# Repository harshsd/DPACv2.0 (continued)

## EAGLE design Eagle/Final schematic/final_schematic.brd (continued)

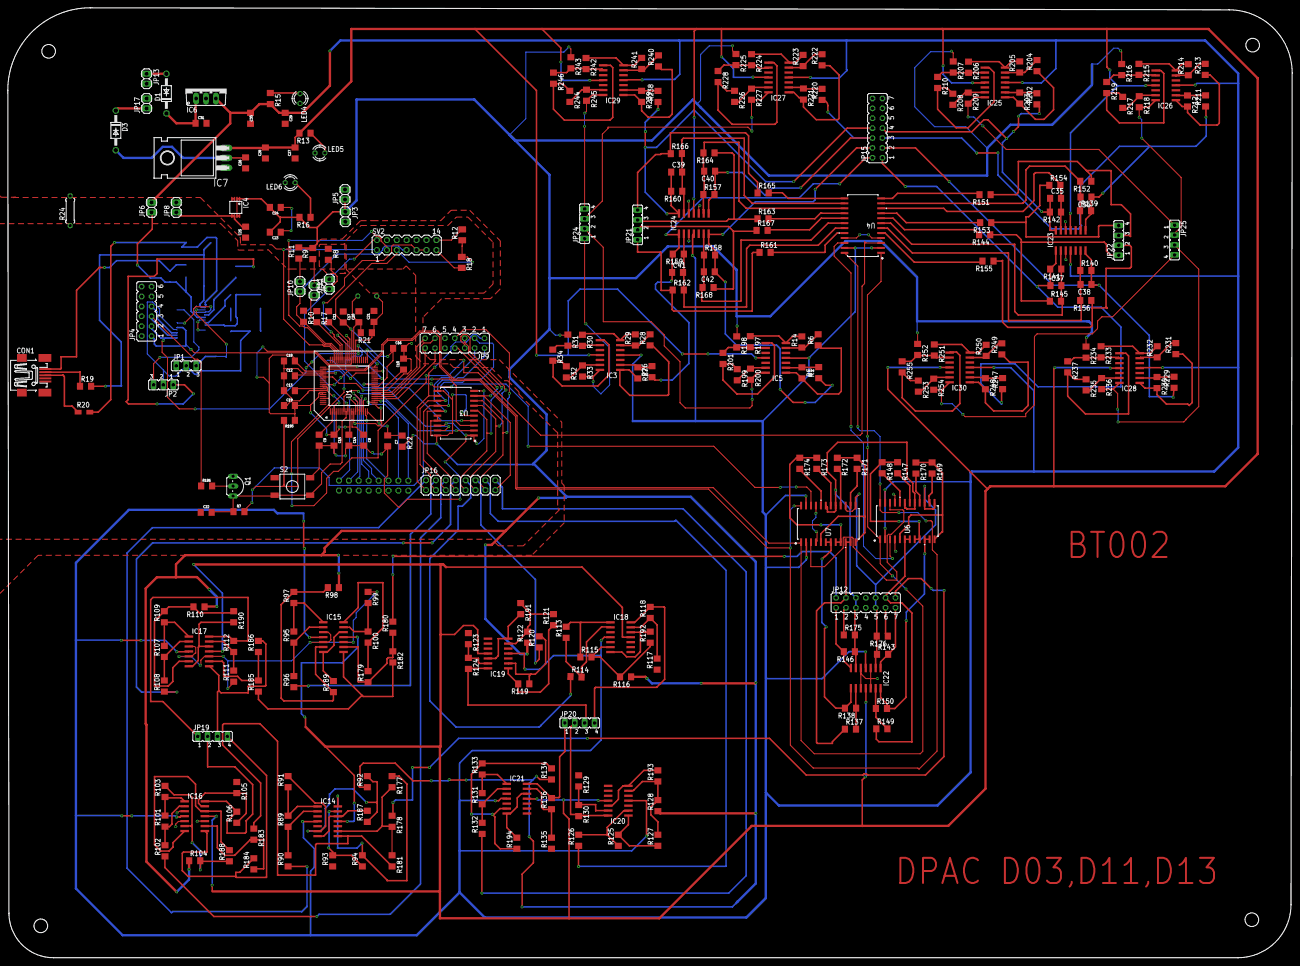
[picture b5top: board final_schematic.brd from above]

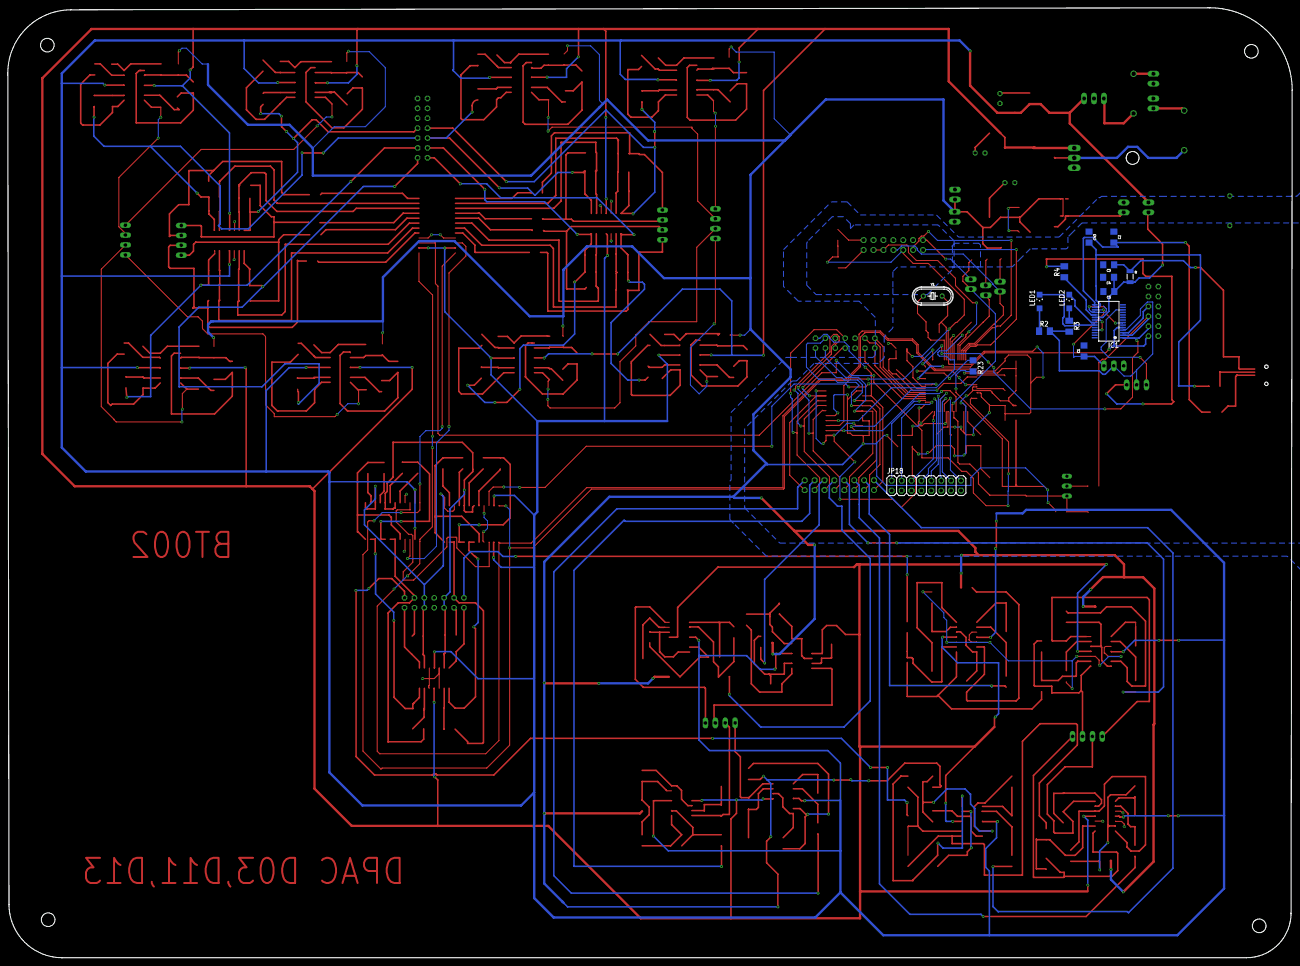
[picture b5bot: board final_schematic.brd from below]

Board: 2 copper layers, 329.5 x 243.7 mm, 303 parts (16 on the bottom side), 272 nets.

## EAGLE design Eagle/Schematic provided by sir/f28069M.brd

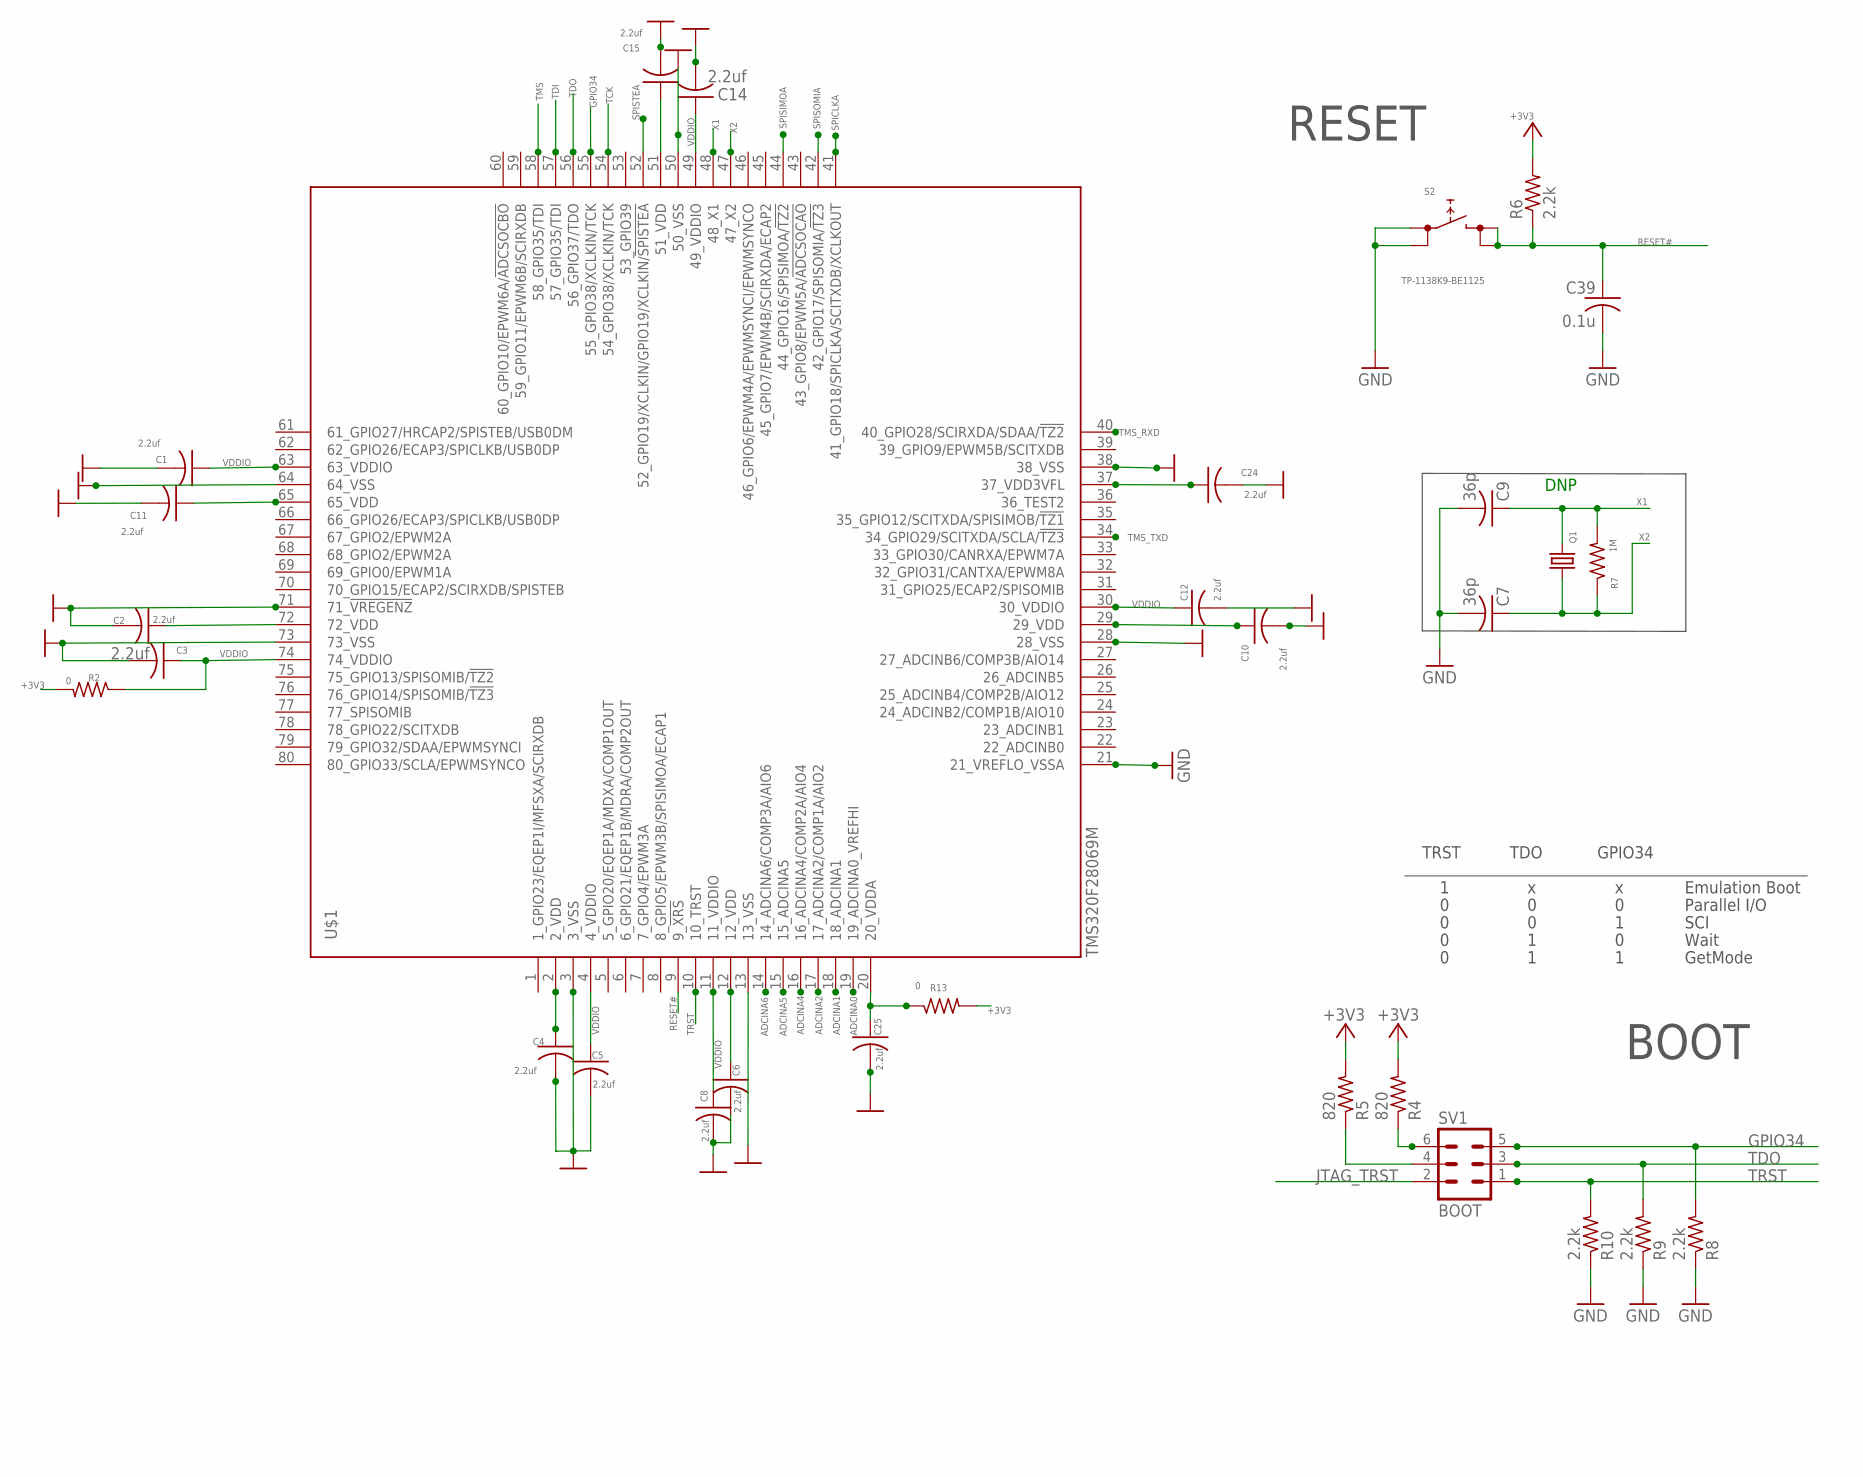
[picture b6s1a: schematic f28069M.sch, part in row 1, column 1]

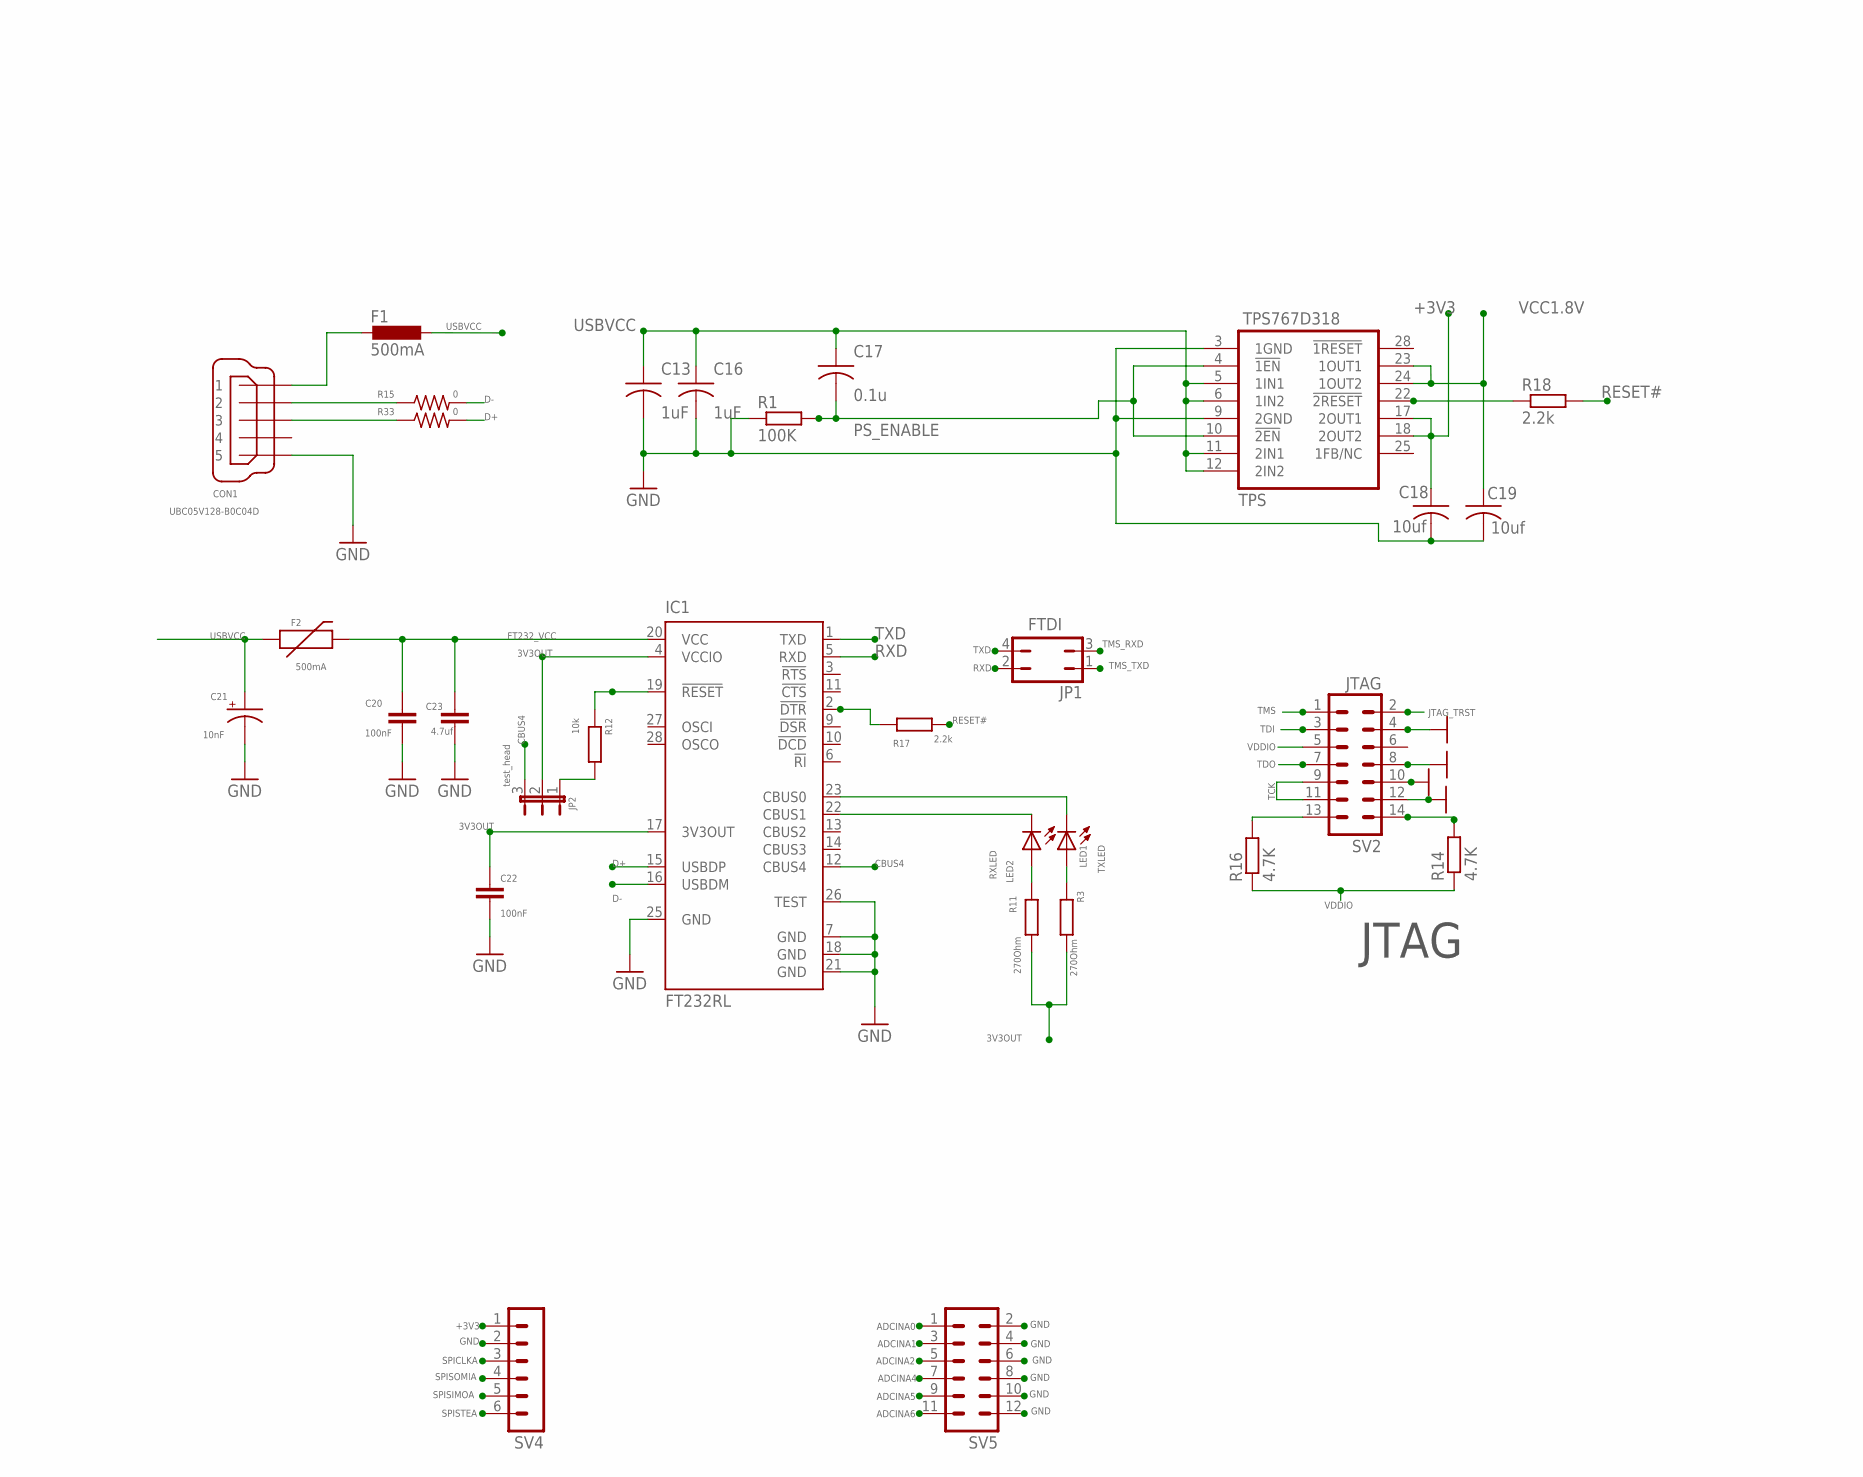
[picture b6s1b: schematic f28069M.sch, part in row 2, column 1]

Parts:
C1, C2, C3, C4, C5, C6, C8, C10, C11, C12, C14, C15, C24, C25: 2.2uf; C1206K
C7, C9: 36p; C1206K
C13, C16: 1uF; C-2,5
C17: 0.1u; C-2,5
C18, C19: 10uf; C-2,5
C20, C22: 100nF; 1210
C21: 10nF; EIA3216
C23: 4.7uf; C2.5-3
C39: 0.1u; C1206K
CON1: UBC05V128-B0C04D; 32005-201
F1: 500mA; L1812
F2: 500mA; PTC-1206
IC1: FT232RL; SSOP28
JP1: FTDI; JP2Q
JP2: test_head; JP2
LED1: TXLED; CHIPLED_1206
LED2: RXLED; CHIPLED_1206
Q1: CRYSTALHC49S; HC49/S
R1: 100K; M1206
R2, R13, R15: 0; R1206
R3, R11: 270Ohm; M1206
R4, R5: 820; R1206
R6, R8, R9, R10: 2.2k; R1206
R7: 1M; R1206
R12: 10k; M1206
R14, R16: 4.7K; M1206
R17, R18: 2.2k; M1206
R33: 0; R1206W
S2: TP-1138K9-BE1125; FSMJSMA
SV1: BOOT; MA03-2
SV2: JTAG; MA07-2
SV4: MA06-1
SV5: MA06-2
TPS: TPS767D318; 767D3XX
U$1: TMS320F28069M; S-PQFP-G80

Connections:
3V3OUT: C22.1, IC1.4 (VCCIO), IC1.17 (3V3OUT), JP2.2, R3.2, R11.2
+3V3: C18.1, R2.2, R4.2, R5.2, R6.2, R13.2, SV4.1, TPS.17 (2OUT1), TPS.18 (2OUT2)
ADCINA0: SV5.1, U$1.19 (19_ADCINA0_VREFHI)
ADCINA1: SV5.3, U$1.18 (18_ADCINA1)
ADCINA2: SV5.5, U$1.17 (17_ADCINA2/COMP1A/AIO2)
ADCINA4: SV5.7, U$1.16 (16_ADCINA4/COMP2A/AIO4)
ADCINA5: SV5.9, U$1.15 (15_ADCINA5)
ADCINA6: SV5.11, U$1.14 (14_ADCINA6/COMP3A/AIO6)
CBUS4: IC1.12 (CBUS4), JP2.3
D+: IC1.15 (USBDP), R33.2
D-: IC1.16 (USBDM), R15.2
FT232_VCC: C20.1, C23.1, F2.2, IC1.20 (VCC)
GND: C1.2, C2.2, C3.2, C4.2, C5.2, C6.2, C7.2, C8.2, C9.2, C10.2, C11.2, C12.2, C13.2, C14.2, C15.2, C16.2, C18.2, C19.2, C20.2, C21.C (-), C22.2, C23.2, C24.2, C25.2, C39.2, CON1.5, IC1.7 (GND), IC1.18 (GND), IC1.21 (GND), IC1.25 (GND), IC1.26 (TEST), R1.1, R8.1, R9.1, R10.1, S2.P$1 (0), S2.P$2 (0), SV2.4, SV2.8, SV2.10, SV2.12, SV4.2, SV5.2, SV5.4, SV5.6, SV5.8, SV5.10, SV5.12, TPS.3 (1GND), TPS.9 (2GND), U$1.3 (3_VSS), U$1.13 (13_VSS), U$1.21 (21_VREFLO_VSSA), U$1.28 (28_VSS), U$1.38 (38_VSS), U$1.50 (50_VSS), U$1.64 (64_VSS), U$1.71 (71_!VREGENZ), U$1.73 (73_VSS)
GPIO34: R8.2, SV1.5, U$1.55 (55_GPIO38/XCLKIN/TCK)
JTAG_TRST: SV1.2, SV2.2
unnamed: C10.1, U$1.29 (29_VDD)
unnamed: R16.2, SV2.13
unnamed: C15.1, U$1.51 (51_VDD)
unnamed: C24.1, U$1.37 (37_VDD3VFL)
unnamed: R4.1, SV1.6
unnamed: R5.1, SV1.4
unnamed: R14.2, SV2.14
unnamed: C11.1, U$1.65 (65_VDD)
unnamed: IC1.2 (!DTR), R17.1
unnamed: R18.1, TPS.22 (!2RESET)
unnamed: C2.1, U$1.72 (72_VDD)
unnamed: C4.1, U$1.2 (2_VDD)
unnamed: C6.1, U$1.12 (12_VDD)
unnamed: LED1.A, R3.1
unnamed: LED2.A, R11.1
unnamed: IC1.23 (CBUS0), LED1.C
unnamed: IC1.22 (CBUS1), LED2.C
unnamed: JP2.1, R12.2
unnamed: CON1.2, R15.1
unnamed: CON1.3, R33.1
PS_ENABLE: C17.2, R1.2, TPS.4 (!1EN), TPS.10 (!2EN)
RESET: IC1.19 (!RESET), R12.1
RESET#: C39.1, R6.1, R17.2, R18.2, S2.P$3 (1), S2.P$4 (1), U$1.9 (9_!XRS)
RXD: IC1.5 (RXD), JP1.2
SPICLKA: SV4.3, U$1.41 (41_GPIO18/SPICLKA/SCITXDB/XCLKOUT)
SPISIMOA: SV4.5, U$1.44 (44_GPIO16/SPISIMOA/!TZ2)
SPISOMIA: SV4.4, U$1.42 (42_GPIO17/SPISOMIA/!TZ3)
SPISTEA: SV4.6, U$1.52 (52_GPIO19/XCLKIN/GPIO19/XCLKIN/!SPISTEA)
TCK: SV2.9, SV2.11, U$1.54 (54_GPIO38/XCLKIN/TCK)
TDI: SV2.3, U$1.57 (57_GPIO35/TDI)
TDO: R9.2, SV1.3, SV2.7, U$1.56 (56_GPIO37/TDO)
TMS: SV2.1, U$1.58 (58_GPIO35/TDI)
TMS_RXD: JP1.3, U$1.40 (40_GPIO28/SCIRXDA/SDAA/!TZ2)
TMS_TXD: JP1.1, U$1.34 (34_GPIO29/SCITXDA/SCLA/!TZ3)
TRST: R10.2, SV1.1, U$1.10 (10_TRST)
TXD: IC1.1 (TXD), JP1.4
USBVCC: C13.1, C16.1, C17.1, C21.A (+), F1.1, F2.1, TPS.5 (1IN1), TPS.6 (1IN2), TPS.11 (2IN1), TPS.12 (2IN2)
VCC1.8V: C19.1, TPS.23 (1OUT1), TPS.24 (1OUT2)
VDDA: C25.1, R13.1, U$1.20 (20_VDDA)
VDDIO: C1.1, C3.1, C5.1, C8.1, C12.1, C14.1, R2.1, R14.1, R16.1, SV2.5, U$1.4 (4_VDDIO), U$1.11 (11_VDDIO), U$1.30 (30_VDDIO), U$1.49 (49_VDDIO), U$1.63 (63_VDDIO), U$1.74 (74_VDDIO)
X1: C9.1, Q1.2, R7.2, U$1.48 (48_X1)
X2: C7.1, Q1.1, R7.1, U$1.47 (47_X2)
XUSB: CON1.1, F1.2

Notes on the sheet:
RESET
TDO
GPIO34
TRST
Emulation Boot
Parallel I/O
SCI
Wait
GetMode
BOOT
DNP
JTAG

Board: 2 copper layers, 61 parts (0 on the bottom side), 58 nets, no tracks yet.

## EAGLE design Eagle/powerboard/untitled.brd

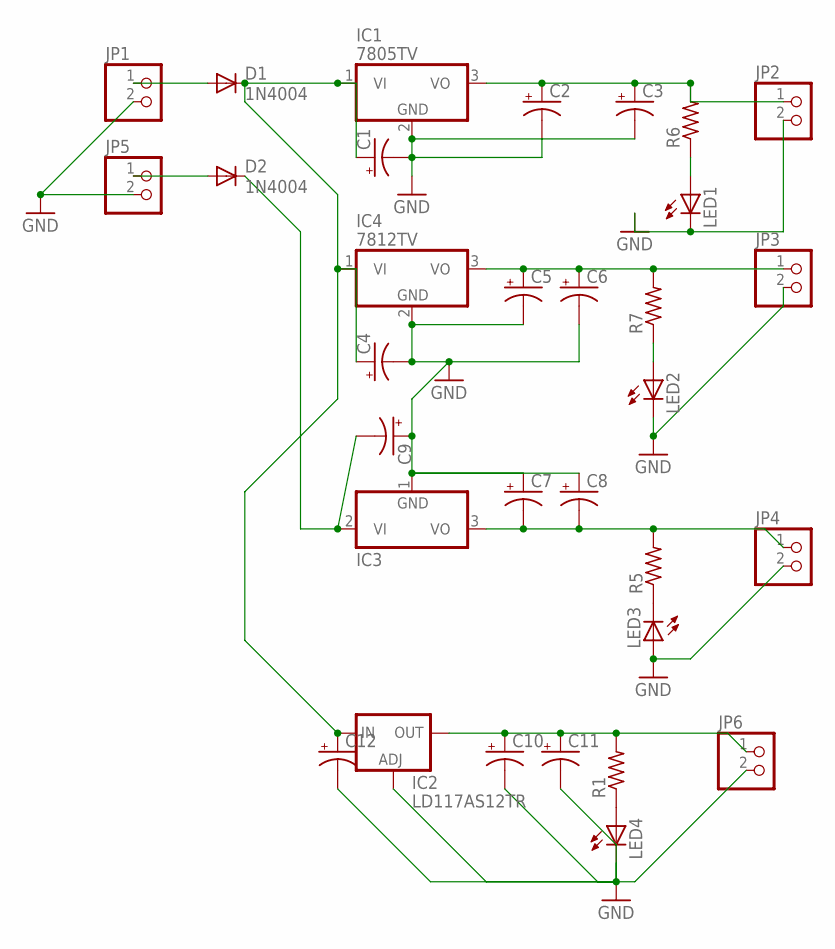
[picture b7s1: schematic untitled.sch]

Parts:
C1, C2, C3, C4, C5, C6, C7, C8, C9, C10, C11, C12: CPOL-USE2.5-5; E2,5-5
D1, D2: 1N4004; DO41-10
IC1: 7805TV; TO220V
IC2: LD117AS12TR; SOT223
IC3: 7912T; TO220H
IC4: 7812TV; TO220V
JP1, JP2, JP3, JP4, JP5, JP6: PINHD-1X2; 1X02
LED1, LED2, LED3, LED4: LED3MM
R1, R5, R6, R7: R-US_R1206; R1206

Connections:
GND: C1.-, C2.-, C3.-, C4.-, C5.-, C6.-, C7.+, C8.+, C9.+, C10.-, C11.-, C12.-, IC1.2 (GND), IC2.1 (ADJ), IC3.1 (GND), IC4.2 (GND), JP1.2, JP2.2, JP3.2, JP4.2, JP5.2, JP6.2, LED1.K (C), LED2.K (C), LED3.A, LED4.K (C)
unnamed: D1.A, JP1.1
unnamed: C9.-, D2.C, IC3.2 (VI)
unnamed: D2.A, JP5.1
unnamed: LED4.A, R1.1
unnamed: LED1.A, R6.1
unnamed: C2.+, C3.+, IC1.3 (VO), JP2.1, R6.2
unnamed: C5.+, C6.+, IC4.3 (VO), JP3.1, R7.2
unnamed: LED2.A, R7.1
unnamed: LED3.K (C), R5.1
unnamed: C7.-, C8.-, IC3.3 (VO), JP4.1, R5.2
unnamed: C1.+, C4.+, C12.+, D1.C, IC1.1 (VI), IC2.3 (IN), IC4.1 (VI)
unnamed: C10.+, C11.+, IC2.4 (OUT), JP6.1, R1.2

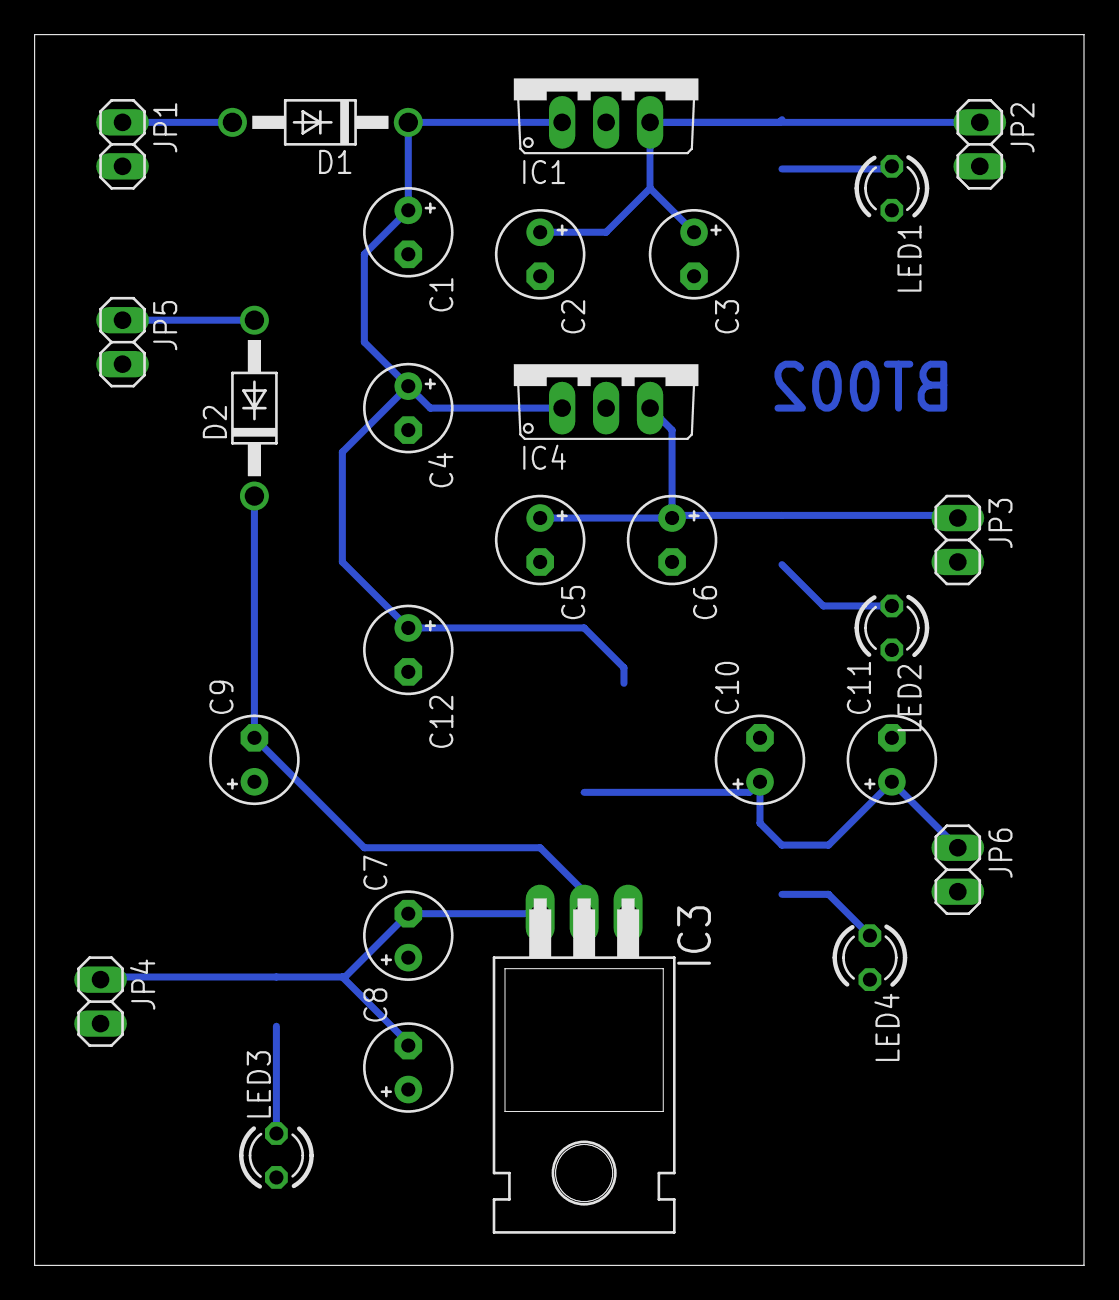
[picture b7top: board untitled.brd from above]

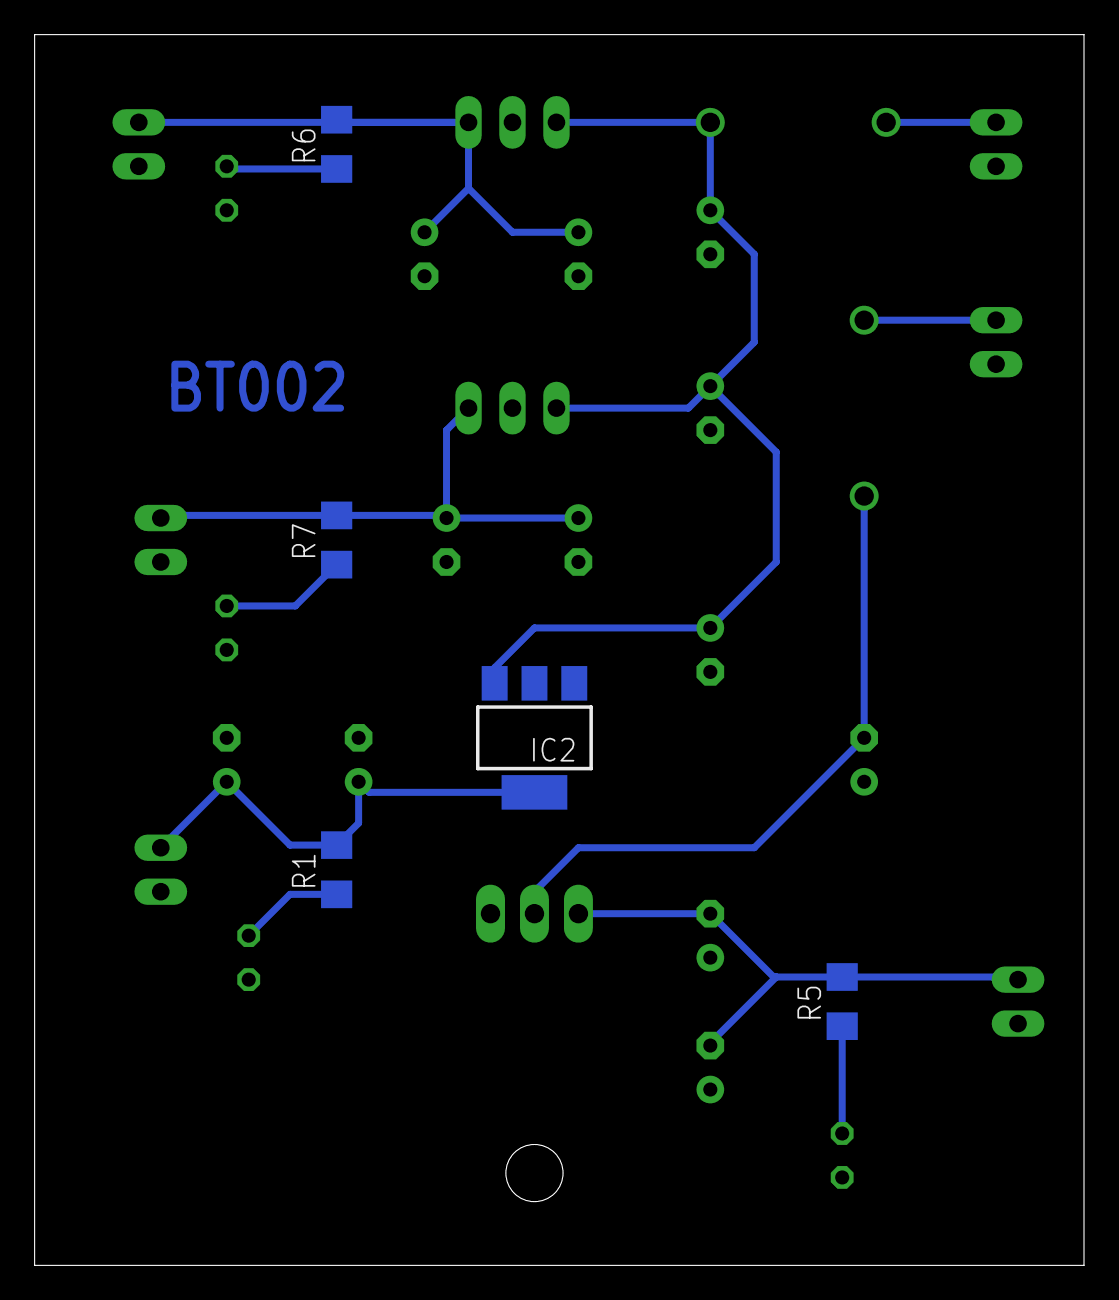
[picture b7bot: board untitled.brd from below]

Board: 2 copper layers, 60.6 x 71.1 mm, 32 parts (5 on the bottom side), 13 nets.

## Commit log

2019-04-15 C++ code left
2019-04-18 test_commit
2019-04-18 datasheets commit
2019-04-18 schematics
2019-04-18 final commit
2019-04-18 dpac codes
2019-04-18 removing readme
2019-04-18 report
2019-04-19 videos 1
2019-04-19 videos 2
2019-04-20 videos 3
2019-04-20 report update
